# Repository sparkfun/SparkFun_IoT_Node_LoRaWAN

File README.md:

SparkFun IoT Node - LoRaWAN
========================================

[*SparkFun IoT Node - LoRaWAN (WRL-26060)*](https://www.sparkfun.com/products/26060)

The SparkFun IoT Node – LoRaWAN development board brings an entirely new level of usability to the often convoluted and configuration-intensive effort to set up a LoRaWAN™-based IoT Device. Combining the ease of LoRaWAN™ setup and configuration delivered by the Digi X-ON™ system with the rapid prototyping provided by the SparkFun Qwiic ecosystem, the SparkFun IoT Node – LoRaWAN development board accelerates IoT end-node creation and deployment.  

**Out of the Box**

With the integration of Digi X-ON™ technology, the SparkFun IoT Node – LoRaWAN board allows the creation and deployment of a LoRaWAN™ IoT sensor in minutes. 

* Set up the Digi HX15 Gateway for LoRaWAN and corresponding Digi account.  
* Register the IoT Node – LoRaWAN board quickly using the digital data block on the module.
* Add the antenna and a supported Qwiic sensor to the Node board 
* Power the board  

The SparkFun IoT Node – LoRaWAN board is shipped with firmware installed that Digi HX15 Gateway for LoRaWAN automatically connects to Digi X-ON, detects an attached sensor, and posts data to the X-ON cloud. Configured via a serial console connection, this application allows rapid evaluation and creation of a LoRaWAN™ IoT device.  

The pre-installed application is also open source and readily available, enabling rapid customization if desired.

**Firmware Development**

The firmware development for the SparkFun IoT Node – LoRaWAN board is performed primarily in the Arduino environment and enabled by an Arduino XBee® LR library from Digi. Combining the easy LoRaWAN™ access provided by the Digi library with the wide range of Qwiic sensors available from SparkFun, the possibilities of potential LoRaWAN™ IoT sensors are endless. 

Additionally, the pre-installed application is open source and readily available, enabling rapid customization if desired.  

**Hardware**

At the heart of the IoT Node – LoRaWAN board is the RP2350 microprocessor from Raspberry Pi, supporting many development environments, including Arduino, micropython, and the Raspberry Pi pico SDK. Besides the capabilities the RP2350 provides, we’ve kitted out the processer with all the goodies your project might require: 

* 16 MB of flash 
* 8 MB PSRAM 
* Qwiic connector 
* On-board Lithium Ion (LiPo) battery charging 
* Fuel gauge circuits 
* microSD card  
* A variety of IO pins 
* RGB LED and user button 

The Digi XBee® LR module for LoRaWAN module is directly connected to a serial port of the RP2350, allowing direct control and access to the LoRaWAN™ module via a development library provided by Digi.  

The XBee® LR for LoRaWAN™ module is the latest LoRaWAN™ module from Digi, delivering unmatched operational performance and onboarding simplicity. The Digi XBee® LR uses LoRa™ modulation for Non-Line-of-Sight (NLOS) two-way communications for long-range and high-noise RF environments. Since each module is pre-activated on Digi's X-ON™ cloud platform, automated connection and two-way device management are a breeze.

Repository Contents
-------------------

* **/Hardware** - KiCAD design files (.brd, .sch)
* **/Documents** - Files related to the hardware on the board
* **/docs** - Hookup guide files

Documentation
--------------
* **[Hookup Guide](https://docs.sparkfun.com/SparkFun_IoT_Node_LoRaWAN)** - Basic hookup guide for the SparkFun IoT Node for LoRaWAN®.
* **[Firmware Guide](https://docs.sparkfun.com/sfe-iot-node-lorawan/)** - Firmware guide for the SparkFun IoT Node for LoRaWAN®.

License Information
-------------------

This product is _**open source**_! 

Please review the LICENSE.md file for license information. 

If you have any questions or concerns on licensing, please contact technical support on our [SparkFun forums](https://forum.sparkfun.com/viewforum.php?f=152).

Distributed as-is; no warranty is given.

- Your friends at SparkFun.

_<COLLABORATION CREDIT>_

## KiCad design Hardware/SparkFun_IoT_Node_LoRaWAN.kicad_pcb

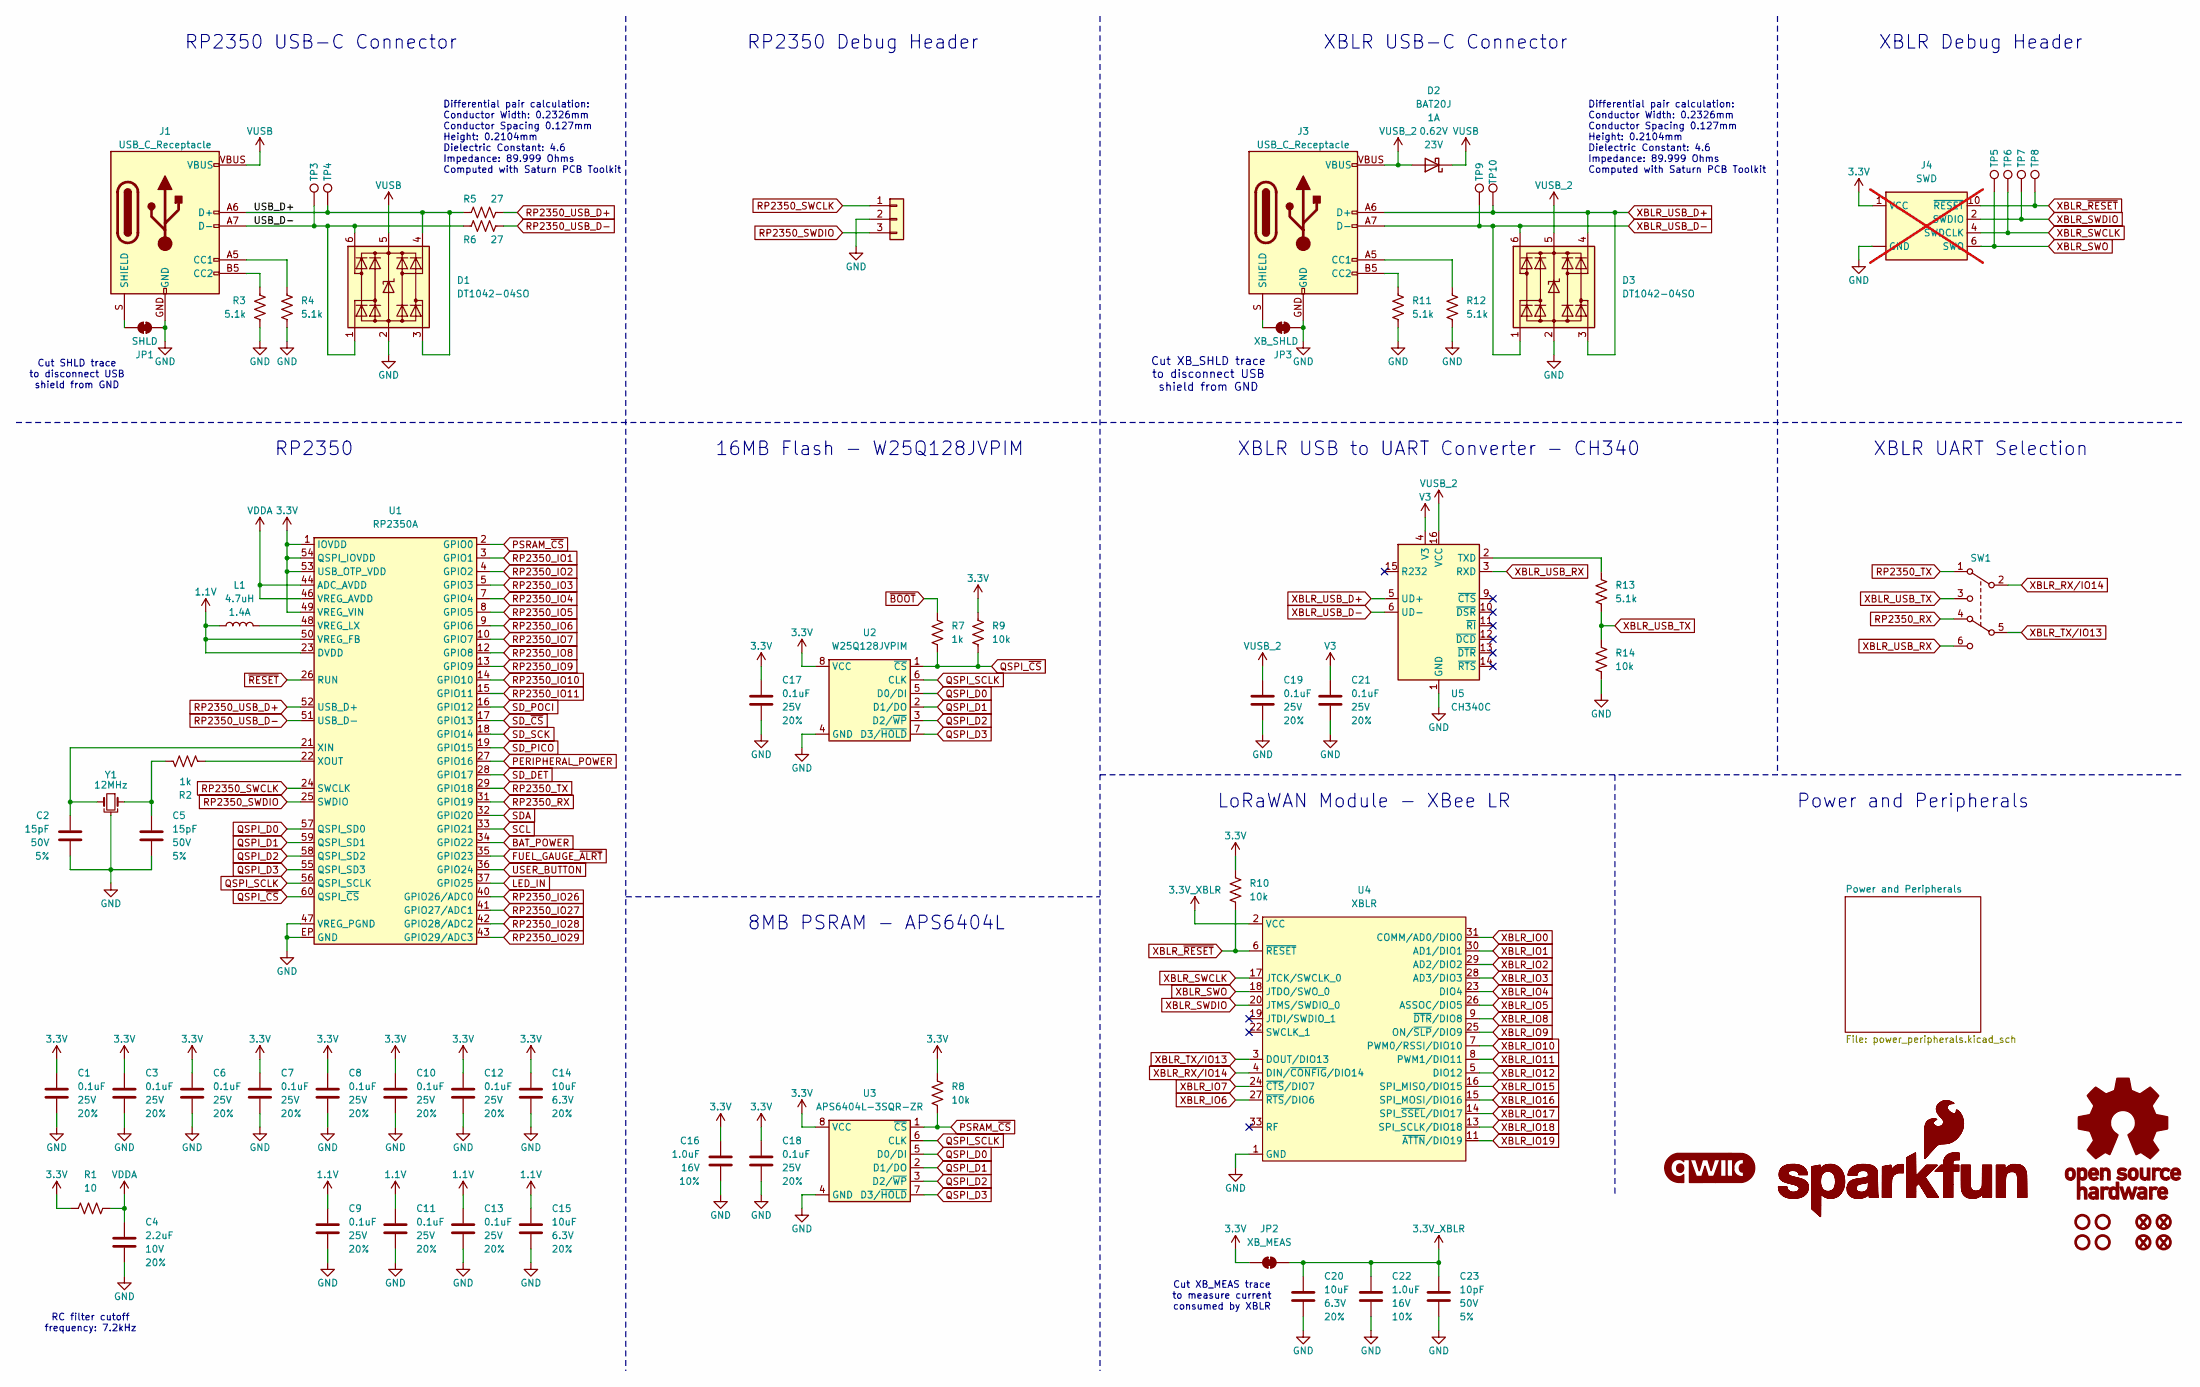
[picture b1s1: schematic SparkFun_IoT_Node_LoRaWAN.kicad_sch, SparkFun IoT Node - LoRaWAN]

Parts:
C1, C3, C6, C7, C8, C9, C10, C11, C12, C13, C17, C18, C19, C21: 0.1uF; C_0603_1608Metric; Voltage 25V; Tolerance 20%
C2, C5: 15pF; C_0603_1608Metric; Voltage 50V; Tolerance 5%
C4: 2.2uF; C_0603_1608Metric; Voltage 10V; Tolerance 20%
C14, C15, C20: 10uF; C_0603_1608Metric; Voltage 6.3V; Tolerance 20%
C16, C22: 1.0uF; C_0603_1608Metric; Voltage 16V; Tolerance 10%
C23: 10pF; C_0603_1608Metric; Voltage 50V; Tolerance 5%
D1, D3: DT1042-04SO; SOT23-6
D2: BAT20J; SOD-323
FID1, FID2, FID3, FID4: Fiducial_0.5mm; Fiducial_0.5mm_Mask1mm
G1: qwiic_Logo
G2: SparkFun_Logo; SparkFun_Logo_8mm
G3: SparkFun_Logo
G4: OSHW_Logo; Creative_Commons_License
J1, J3: USB_C_Receptacle; USB-C_16
J2: Conn_01x03; 1x03
J4: SWD; 2x5_1.27mm_SMD_Unshrouded; not fitted
JP1: SHLD; Jumper_2_NC_Trace
JP2: XB_MEAS; Jumper_2_PTH_SMD_Combo-NC
JP3: XB_SHLD; Jumper_2_NC_Trace
L1: 4.7uH; 1008_2520Metric
R1: 10; R_0603_1608Metric
R2, R7: 1k; R_0603_1608Metric
R3, R4, R11, R12, R13: 5.1k; R_0603_1608Metric
R5, R6: 27; R_0603_1608Metric
R8, R9, R10, R14: 10k; R_0603_1608Metric
ST1, ST2, ST3, ST4: Standoff
SW1: DPDT_Slide_SMD_7.2x3.5mm; Slide_DPDT_SMD_7.2x3.5mm; Mfg Part# ABC
TP3, TP4, TP5, TP6, TP7, TP8, TP9, TP10: 1.0mm; TestPoint-1.0mm
U1: RP2350A; QFN-60-1EP_7x7mm_P0.4mm_EP3.5x3.5mm
U2: W25Q128JVPIM; WDFN-8_6x5mm-SkinnyCenterPad
U3: APS6404L-3SQR-ZR; USON-8_3x2mm-SkinnyCenterPad
U4: XBLR; XBee_LR
U5: CH340C; SO-16
Y1: 12MHz; Crystal_SMD_2.5x2.0mm

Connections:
1.1V: C9.1, C11.1, C13.1, C15.1, L1.1, U1.6 (DVDD), U1.23 (DVDD), U1.39 (DVDD), U1.50 (VREG_FB)
3.3V: C1.1, C3.1, C6.1, C7.1, C8.1, C10.1, C12.1, C14.1, C16.1, C17.1, C18.1, J4.1 (VCC), JP2.1 (A), R1.2, R8.1, R9.1, R10.1, U1.1 (IOVDD), U1.11 (IOVDD), U1.20 (IOVDD), U1.30 (IOVDD), U1.38 (IOVDD), U1.45 (IOVDD), U1.49 (VREG_VIN), U1.53 (USB_OTP_VDD), U1.54 (QSPI_IOVDD), U2.8 (VCC), U3.8 (VCC); also elsewhere on the board
3.3V_XBLR: C20.1, C22.1, C23.1, JP2.2 (B), U4.2 (VCC)
/USB_D+: D1.3 (I/O2), D1.4 (I/O3), J1.A6 (D+), J1.B6 (D+), R5.2, TP4.1
/USB_D-: D1.1 (I/O1), D1.6 (I/O4), J1.A7 (D-), J1.B7 (D-), R6.2, TP3.1
BAT_POWER: U1.34 (GPIO22); also elsewhere on the board
FUEL_GAUGE_~ALRT: U1.35 (GPIO23); also elsewhere on the board
GND: C1.2, C2.1, C3.2, C4.2, C5.1, C6.2, C7.2, C8.2, C9.2, C10.2, C11.2, C12.2, C13.2, C14.2, C15.2, C16.2, C17.2, C18.2, C19.2, C20.2, C21.2, C22.2, C23.2, D1.2 (GND), D3.2 (GND), J1.GND, J2.2, J3.GND, J4.3 (GND), J4.5 (GND), J4.9 (GND), JP1.2 (B), JP3.2 (B), R3.2, R4.2, R11.2, R12.2, R14.2, U1.47 (VREG_PGND), U1.EP (GND), U2.4 (GND), U3.4 (GND), U3.9 (GND), U4.1 (GND), U4.10 (GND), U4.12 (GND), U4.21 (GND), U4.32 (GND), U4.34 (GND), U5.1 (GND), Y1.2, Y1.4; also elsewhere on the board
LED_IN: U1.37 (GPIO25); also elsewhere on the board
unnamed: C5.2, R2.2, Y1.1
unnamed: J1.A5 (CC1), R4.1
unnamed: J1.B5 (CC2), R3.1
unnamed: J1.S (SHIELD), JP1.1 (A)
unnamed: J3.A5 (CC1), R12.1
unnamed: J3.B5 (CC2), R11.1
unnamed: J3.S (SHIELD), JP3.1 (A)
unnamed: L1.2, U1.48 (VREG_LX)
unnamed: C2.2, U1.21 (XIN), Y1.3
unnamed: R2.1, U1.22 (XOUT)
unnamed: R13.1, U5.2 (TXD)
PERIPHERAL_POWER: U1.27 (GPIO16); also elsewhere on the board
PSRAM_~CS: R8.2, U1.2 (GPIO0), U3.1 (~CS)
QSPI_D0: U1.57 (QSPI_SD0), U2.5 (D0/DI), U3.5 (D0/DI)
QSPI_D1: U1.59 (QSPI_SD1), U2.2 (D1/DO), U3.2 (D1/DO)
QSPI_D2: U1.58 (QSPI_SD2), U2.3 (D2/~WP), U3.3 (D2/~WP)
QSPI_D3: U1.55 (QSPI_SD3), U2.7 (D3/~HOLD), U3.7 (D3/~HOLD)
QSPI_SCLK: U1.56 (QSPI_SCLK), U2.6 (CLK), U3.6 (CLK)
QSPI_~CS: R7.2, R9.2, U1.60 (QSPI_~CS), U2.1 (~CS)
RP2350_IO1: U1.3 (GPIO1); also elsewhere on the board
RP2350_IO2: U1.4 (GPIO2); also elsewhere on the board
RP2350_IO3: U1.5 (GPIO3); also elsewhere on the board
RP2350_IO4: U1.7 (GPIO4); also elsewhere on the board
RP2350_IO5: U1.8 (GPIO5); also elsewhere on the board
RP2350_IO6: U1.9 (GPIO6); also elsewhere on the board
RP2350_IO7: U1.10 (GPIO7); also elsewhere on the board
RP2350_IO8: U1.12 (GPIO8); also elsewhere on the board
RP2350_IO9: U1.13 (GPIO9); also elsewhere on the board
RP2350_IO10: U1.14 (GPIO10); also elsewhere on the board
RP2350_IO11: U1.15 (GPIO11); also elsewhere on the board
RP2350_IO26: U1.40 (GPIO26/ADC0); also elsewhere on the board
RP2350_IO27: U1.41 (GPIO27/ADC1); also elsewhere on the board
RP2350_IO28: U1.42 (GPIO28/ADC2); also elsewhere on the board
RP2350_IO29: U1.43 (GPIO29/ADC3); also elsewhere on the board
RP2350_RX: SW1.4 (A), U1.31 (GPIO19)
RP2350_SWCLK: J2.1, U1.24 (SWCLK)
RP2350_SWDIO: J2.3, U1.25 (SWDIO)
RP2350_TX: SW1.1 (A), U1.29 (GPIO18)
RP2350_USB_D+: R5.1, U1.52 (USB_D+)
RP2350_USB_D-: R6.1, U1.51 (USB_D-)
SCL: U1.33 (GPIO21); also elsewhere on the board
SDA: U1.32 (GPIO20); also elsewhere on the board
SD_DET: U1.28 (GPIO17); also elsewhere on the board
SD_PICO: U1.19 (GPIO15); also elsewhere on the board
SD_POCI: U1.16 (GPIO12); also elsewhere on the board
SD_SCK: U1.18 (GPIO14); also elsewhere on the board
SD_~CS: U1.17 (GPIO13); also elsewhere on the board
USER_BUTTON: U1.36 (GPIO24); also elsewhere on the board
V3: C21.1, U5.4 (V3)
VDDA: C4.1, R1.1, U1.44 (ADC_AVDD), U1.46 (VREG_AVDD); also elsewhere on the board
VUSB: D1.5 (VCC), D2.C, J1.VBUS; also elsewhere on the board
VUSB_2: C19.1, D2.A, D3.5 (VCC), J3.VBUS, U5.16 (VCC)
XBLR_IO0: U4.31 (COMM/AD0/DIO0); also elsewhere on the board
XBLR_IO1: U4.30 (AD1/DIO1); also elsewhere on the board
XBLR_IO2: U4.29 (AD2/DIO2); also elsewhere on the board
XBLR_IO3: U4.28 (AD3/DIO3); also elsewhere on the board
XBLR_IO4: U4.23 (DIO4); also elsewhere on the board
XBLR_IO5: U4.26 (ASSOC/DIO5); also elsewhere on the board
XBLR_IO6: U4.27 (~RTS/DIO6); also elsewhere on the board
XBLR_IO7: U4.24 (~CTS/DIO7); also elsewhere on the board
XBLR_IO8: U4.9 (~DTR/DIO8); also elsewhere on the board
XBLR_IO9: U4.25 (ON/~SLP/DIO9); also elsewhere on the board
XBLR_IO10: U4.7 (PWM0/RSSI/DIO10); also elsewhere on the board
XBLR_IO11: U4.8 (PWM1/DIO11); also elsewhere on the board
XBLR_IO12: U4.5 (DIO12); also elsewhere on the board
XBLR_IO15: U4.16 (SPI_MISO/DIO15); also elsewhere on the board
XBLR_IO16: U4.15 (SPI_MOSI/DIO16); also elsewhere on the board
XBLR_IO17: U4.14 (SPI_~SSEL/DIO17); also elsewhere on the board
XBLR_IO18: U4.13 (SPI_SCLK/DIO18); also elsewhere on the board
XBLR_IO19: U4.11 (~ATTN/DIO19); also elsewhere on the board
XBLR_RX/IO14: SW1.2 (B), U4.4 (DIN/~CONFIG/DIO14); also elsewhere on the board
XBLR_SWCLK: J4.4 (SWDCLK), TP6.1, U4.17 (JTCK/SWCLK_0)
XBLR_SWDIO: J4.2 (SWDIO), TP7.1, U4.20 (JTMS/SWDIO_0)
XBLR_SWO: J4.6 (SWO), TP5.1, U4.18 (JTDO/SWO_0)
XBLR_TX/IO13: SW1.5 (B), U4.3 (DOUT/DIO13); also elsewhere on the board
XBLR_USB_D+: D3.3 (I/O2), D3.4 (I/O3), J3.A6 (D+), J3.B6 (D+), TP10.1, U5.5 (UD+)
XBLR_USB_D-: D3.1 (I/O1), D3.6 (I/O4), J3.A7 (D-), J3.B7 (D-), TP9.1, U5.6 (UD-)
XBLR_USB_RX: SW1.6 (C), U5.3 (RXD)
XBLR_USB_TX: R13.2, R14.1, SW1.3 (C)
XBLR_~RESET: J4.10 (~RESET), R10.2, TP8.1, U4.6 (~RESET)
~BOOT: R7.1; also elsewhere on the board
~RESET: U1.26 (RUN); also elsewhere on the board

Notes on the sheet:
Differential pair calculation: Conductor Width: 0.2326mm Conductor Spacing 0.127mm Height: 0.2104mm Dielectric Constant: 4.6 Impedance: 89.999 Ohms Computed with Saturn PCB Toolkit
16MB Flash - W25Q128JVPIM
8MB PSRAM - APS6404L
XBLR USB-C Connector
RP2350 Debug Header
XBLR USB to UART Converter - CH340
RP2350
Cut XB_MEAS trace to measure current consumed by XBLR
Cut SHLD trace to disconnect USB shield from GND
XBLR Debug Header
RC filter cutoff frequency: 7.2kHz
Cut XB_SHLD trace to disconnect USB shield from GND
LoRaWAN Module - XBee LR
XBLR UART Selection
RP2350 USB-C Connector
Power and Peripherals

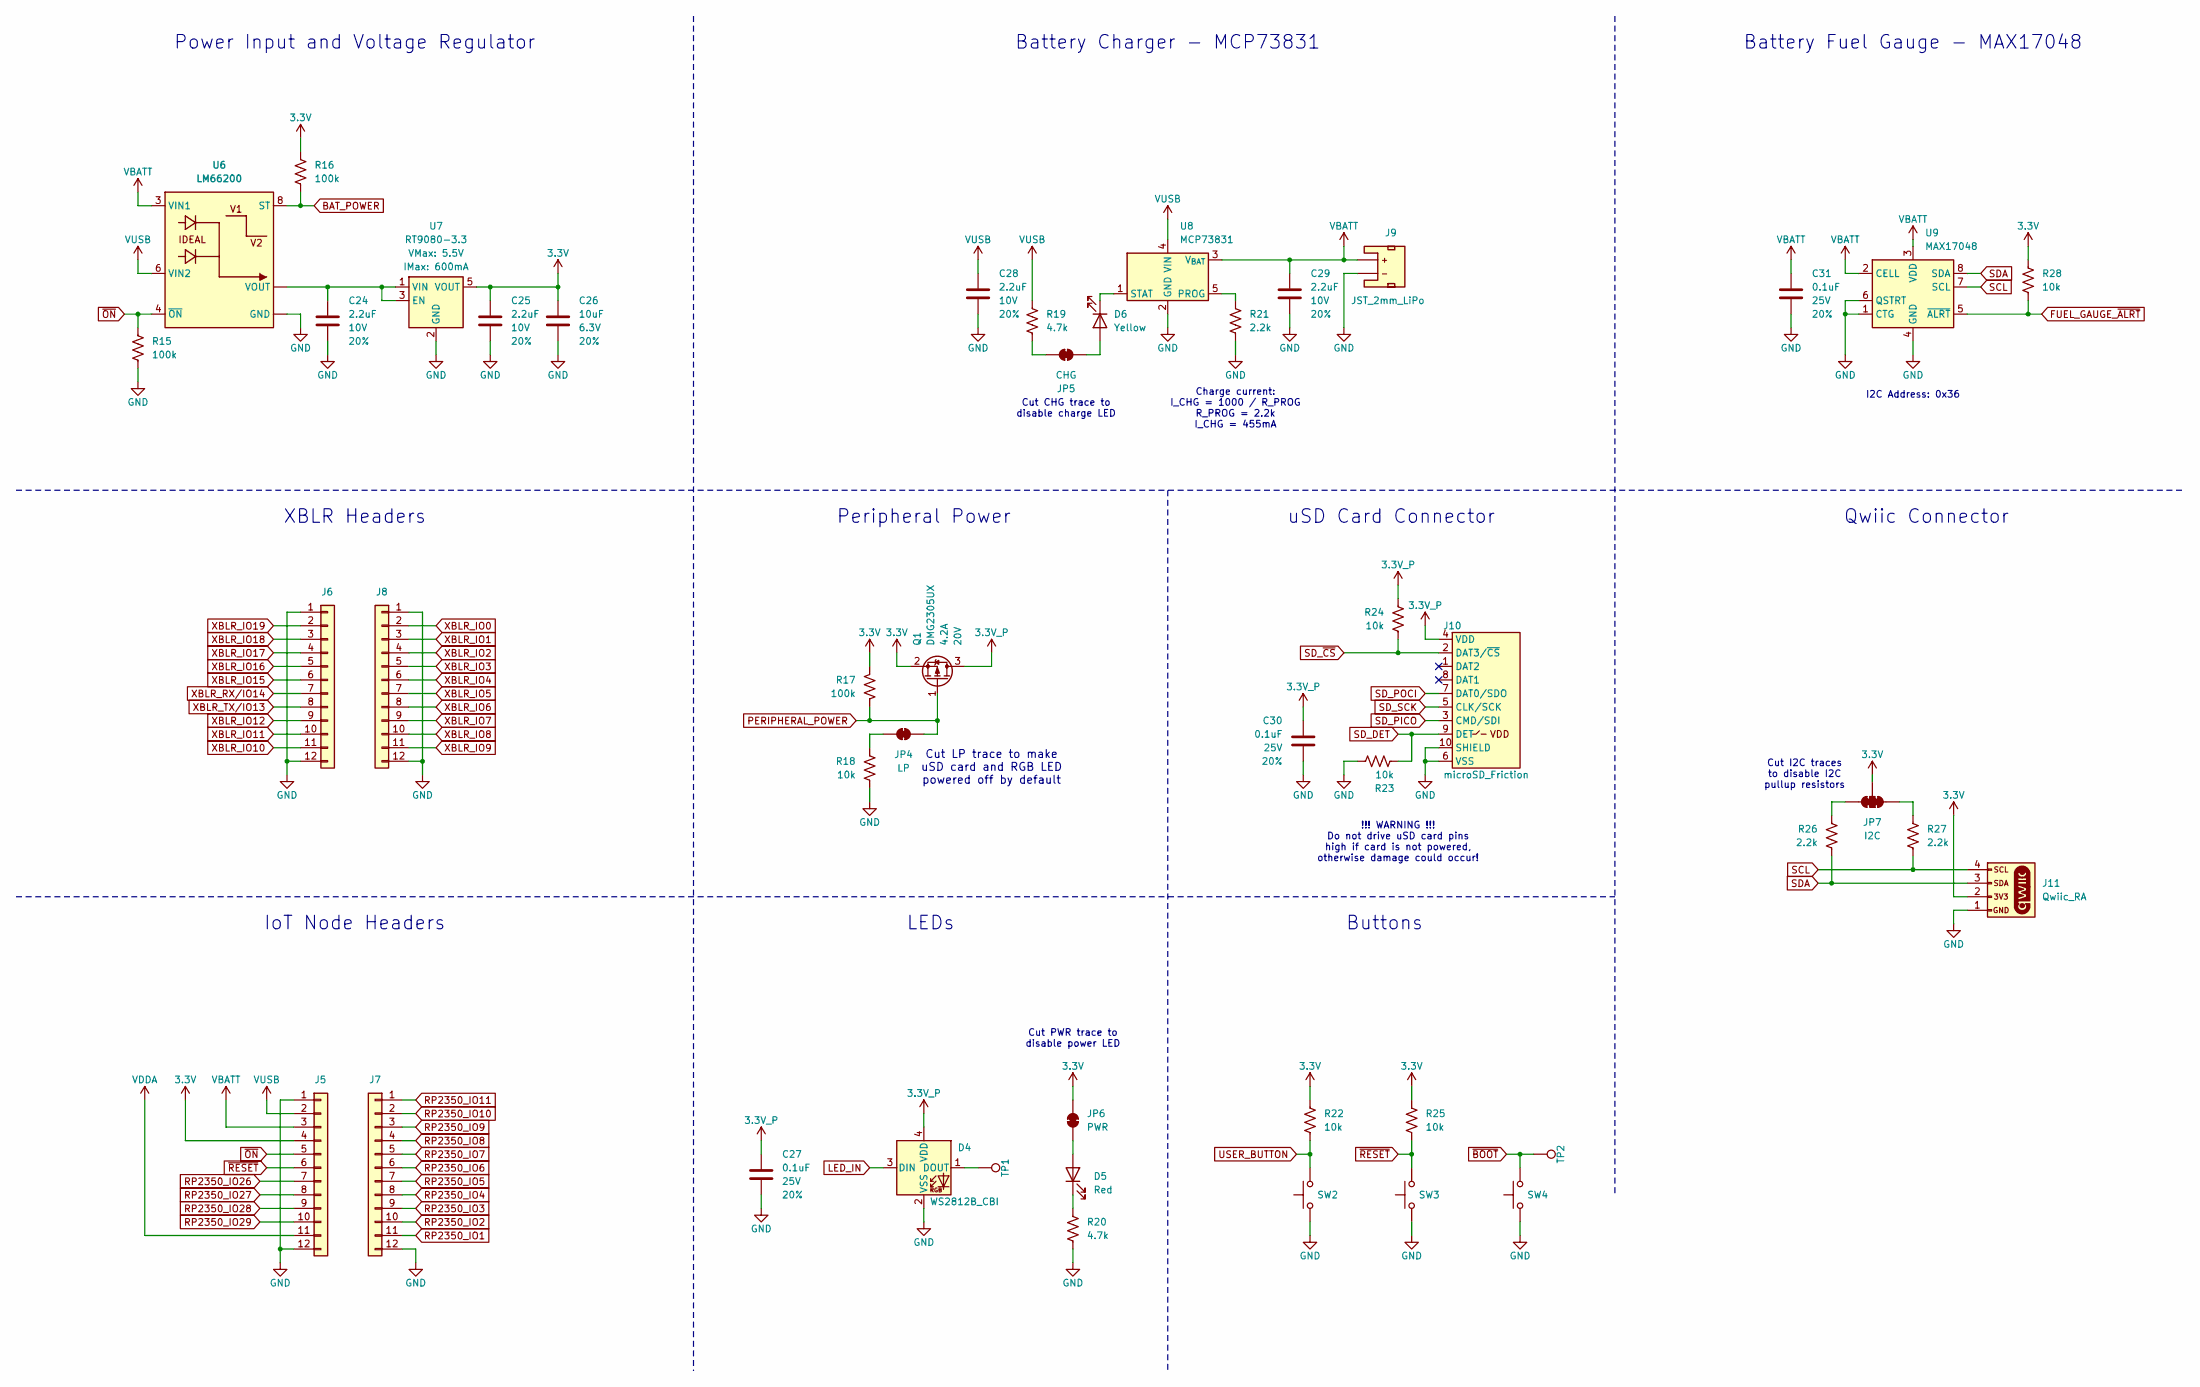
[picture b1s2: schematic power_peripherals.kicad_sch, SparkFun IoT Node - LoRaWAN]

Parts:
C24, C25, C28, C29: 2.2uF; C_0603_1608Metric; Voltage 10V; Tolerance 20%
C26: 10uF; C_0603_1608Metric; Voltage 6.3V; Tolerance 20%
C27, C30, C31: 0.1uF; C_0603_1608Metric; Voltage 25V; Tolerance 20%
D4: WS2812B_CBI; WS2812_2020
D5: Red; LED_0603_1608Metric_Red
D6: Yellow; LED_0603_1608Metric_Yellow
J5, J6, J7, J8: Conn_01x10; 1x12
J9: JST_2mm_LiPo; JST_SMD_2.0mm-2
J10: microSD_Friction; microSD_Friction_Fit_Common
J11: Qwiic_RA; JST_SMD_1.0mm-4_RA
JP4: LP; Jumper_2_NC_Trace
JP5: CHG; Jumper_2_NC_Trace
JP6: PWR; Jumper_2_NC_Trace
JP7: I2C; Jumper_3_NC-2_Trace
Q1: DMG2305UX; SOT23-3
R15, R16, R17: 100k; R_0603_1608Metric
R18, R22, R23, R24, R25, R28: 10k; R_0603_1608Metric
R19, R20: 4.7k; R_0603_1608Metric
R21, R26, R27: 2.2k; R_0603_1608Metric
SW2, SW3, SW4: SMD_4.6x2.8mm_h2.5mm; Push_SMD_4.6x2.8mm_h2.5mm
TP1, TP2: 1.0mm; TestPoint-1.0mm
U6: LM66200; SOT-583-8
U7: RT9080-3.3; SOT23-5
U8: MCP73831; SOT23-5
U9: MAX17048; DFN-8

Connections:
3.3V: C25.1, C26.1, J5.4, J11.2, JP6.2 (B), JP7.2 (C), Q1.2 (S), R16.1, R17.1, R22.1, R25.1, R28.1, U7.5 (VOUT); also elsewhere on the board
3.3V_P: C27.1, C30.1, D4.4 (VDD), J10.4 (VDD), Q1.3 (D), R24.1
BAT_POWER: R16.2, U6.8 (ST); also elsewhere on the board
FUEL_GAUGE_~ALRT: R28.2, U9.5 (~ALRT); also elsewhere on the board
GND: C24.2, C25.2, C26.2, C27.2, C28.2, C29.2, C30.2, C31.2, D4.2 (VSS), J5.1, J5.12, J6.1, J6.12, J7.12, J8.1, J8.12, J9.1 (-), J10.6 (VSS), J10.10 (SHIELD), J11.1, R15.2, R18.2, R20.2, R21.2, R23.2, SW2.1, SW3.1, SW4.1, U6.1 (GND), U6.5 (GND), U7.2 (GND), U8.2 (GND), U9.1 (CTG), U9.4 (GND), U9.6 (QSTRT), U9.9 (GND); also elsewhere on the board
LED_IN: D4.3 (DIN); also elsewhere on the board
unnamed: D4.1 (DOUT), TP1.1
unnamed: D5.2 (A), JP6.1 (A)
unnamed: D5.1 (K), R20.1
unnamed: D6.2 (A), JP5.2 (B)
unnamed: D6.1 (K), U8.1 (STAT)
unnamed: JP4.1 (A), R18.1
unnamed: JP5.1 (A), R19.2
unnamed: JP7.1 (A), R27.1
unnamed: JP7.3 (B), R26.1
unnamed: C24.1, U6.2 (VOUT), U6.7 (VOUT), U7.1 (VIN), U7.3 (EN)
unnamed: R21.1, U8.5 (PROG)
PERIPHERAL_POWER: JP4.2 (B), Q1.1 (G), R17.2; also elsewhere on the board
RP2350_IO1: J7.11; also elsewhere on the board
RP2350_IO2: J7.10; also elsewhere on the board
RP2350_IO3: J7.9; also elsewhere on the board
RP2350_IO4: J7.8; also elsewhere on the board
RP2350_IO5: J7.7; also elsewhere on the board
RP2350_IO6: J7.6; also elsewhere on the board
RP2350_IO7: J7.5; also elsewhere on the board
RP2350_IO8: J7.4; also elsewhere on the board
RP2350_IO9: J7.3; also elsewhere on the board
RP2350_IO10: J7.2; also elsewhere on the board
RP2350_IO11: J7.1; also elsewhere on the board
RP2350_IO26: J5.7; also elsewhere on the board
RP2350_IO27: J5.8; also elsewhere on the board
RP2350_IO28: J5.9; also elsewhere on the board
RP2350_IO29: J5.10; also elsewhere on the board
SCL: J11.4, R27.2, U9.7 (SCL); also elsewhere on the board
SDA: J11.3, R26.2, U9.8 (SDA); also elsewhere on the board
SD_DET: J10.9 (DET), R23.1; also elsewhere on the board
SD_PICO: J10.3 (CMD/SDI); also elsewhere on the board
SD_POCI: J10.7 (DAT0/SDO); also elsewhere on the board
SD_SCK: J10.5 (CLK/SCK); also elsewhere on the board
SD_~CS: J10.2 (DAT3/~CS), R24.2; also elsewhere on the board
USER_BUTTON: R22.2, SW2.2; also elsewhere on the board
VBATT: C29.1, C31.1, J5.3, J9.2 (+), U6.3 (VIN1), U8.3 (V_{BAT}), U9.2 (CELL), U9.3 (VDD)
VDDA: J5.11; also elsewhere on the board
VUSB: C28.1, J5.2, R19.1, U6.6 (VIN2), U8.4 (VIN); also elsewhere on the board
XBLR_IO0: J8.2; also elsewhere on the board
XBLR_IO1: J8.3; also elsewhere on the board
XBLR_IO2: J8.4; also elsewhere on the board
XBLR_IO3: J8.5; also elsewhere on the board
XBLR_IO4: J8.6; also elsewhere on the board
XBLR_IO5: J8.7; also elsewhere on the board
XBLR_IO6: J8.8; also elsewhere on the board
XBLR_IO7: J8.9; also elsewhere on the board
XBLR_IO8: J8.10; also elsewhere on the board
XBLR_IO9: J8.11; also elsewhere on the board
XBLR_IO10: J6.11; also elsewhere on the board
XBLR_IO11: J6.10; also elsewhere on the board
XBLR_IO12: J6.9; also elsewhere on the board
XBLR_IO15: J6.6; also elsewhere on the board
XBLR_IO16: J6.5; also elsewhere on the board
XBLR_IO17: J6.4; also elsewhere on the board
XBLR_IO18: J6.3; also elsewhere on the board
XBLR_IO19: J6.2; also elsewhere on the board
XBLR_RX/IO14: J6.7; also elsewhere on the board
XBLR_TX/IO13: J6.8; also elsewhere on the board
~BOOT: SW4.2, TP2.1; also elsewhere on the board
~ON: J5.5, R15.1, U6.4 (~ON)
~RESET: J5.6, R25.2, SW3.2; also elsewhere on the board

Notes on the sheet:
LEDs
Buttons
Cut LP trace to make uSD card and RGB LED powered off by default
I2C Address: 0x36
Charge current: I_CHG = 1000 / R_PROG R_PROG = 2.2k I_CHG = 455mA
Cut CHG trace to disable charge LED
Peripheral Power
Battery Charger - MCP73831
!!! WARNING !!! Do not drive uSD card pins high if card is not powered, otherwise damage could occur!
Cut I2C traces to disable I2C pullup resistors
uSD Card Connector
IoT Node Headers
Power Input and Voltage Regulator
XBLR Headers
Cut PWR trace to disable power LED
Battery Fuel Gauge - MAX17048
Qwiic Connector

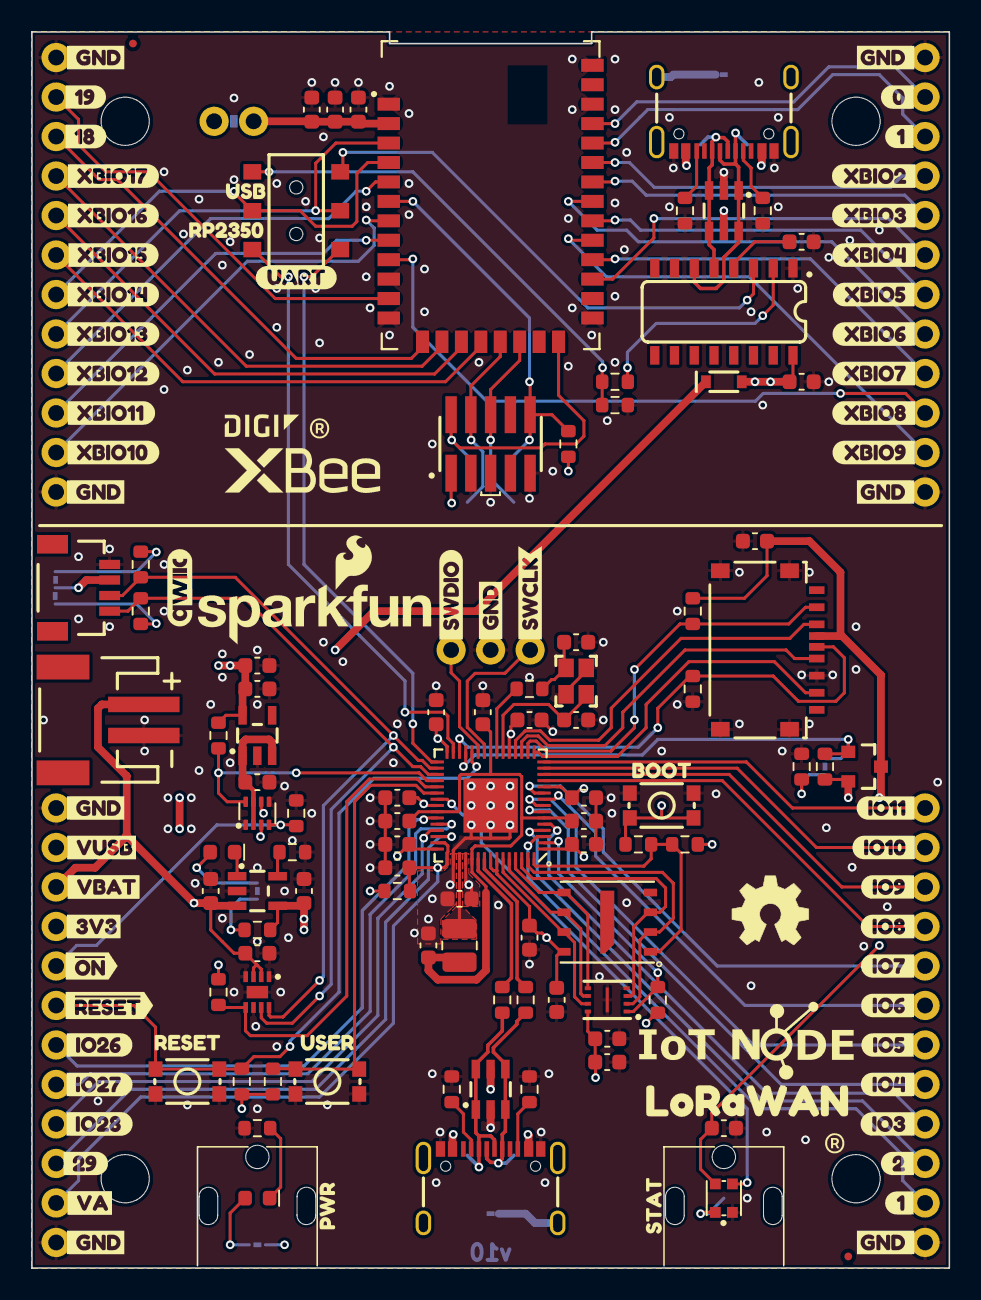
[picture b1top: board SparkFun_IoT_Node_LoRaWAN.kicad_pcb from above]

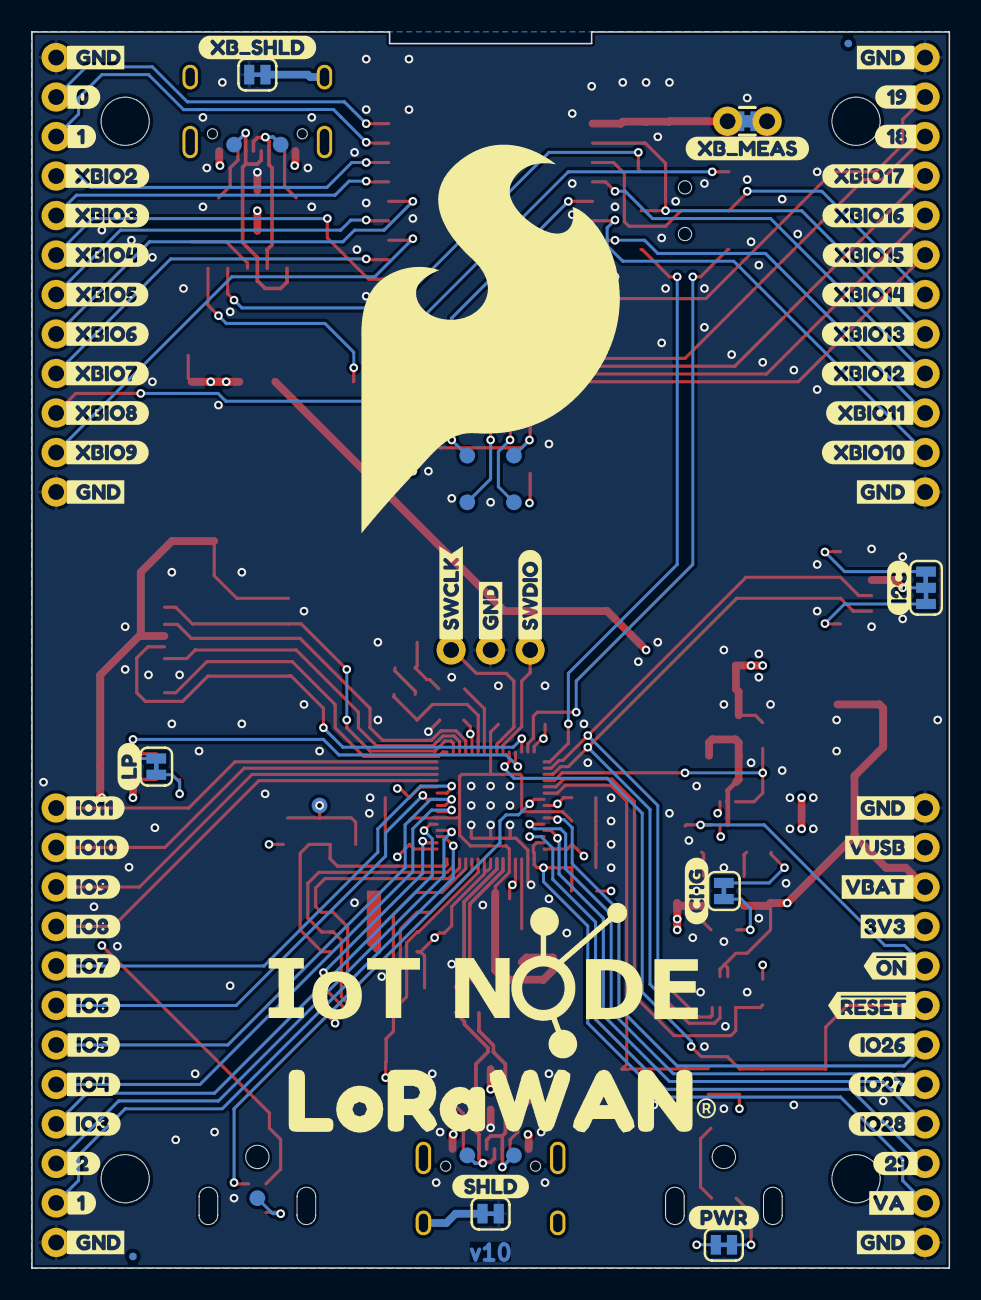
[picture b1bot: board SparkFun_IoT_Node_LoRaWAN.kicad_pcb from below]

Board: 4 copper layers, 59.0 x 79.5 mm, 238 parts (78 on the bottom side), 105 nets.

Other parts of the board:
Ref**: Val**; OSHW_Logo_5mm
kibuzzard-669A9B0A: G***; kibuzzard-669A9B0A
kibuzzard-669E9F4F: G***; kibuzzard-669E9F4F
kibuzzard-669E9F62: G***; kibuzzard-669E9F62
kibuzzard-669E97BF: G***; kibuzzard-669E97BF
kibuzzard-669E97C2: G***; kibuzzard-669E97C2
kibuzzard-669E97C7: G***; kibuzzard-669E97C7
kibuzzard-669E97CC: G***; kibuzzard-669E97CC
kibuzzard-669E97CF: G***; kibuzzard-669E97CF
kibuzzard-669E97D3: G***; kibuzzard-669E97D3
kibuzzard-669E97D7: G***; kibuzzard-669E97D7
kibuzzard-669E97DA: G***; kibuzzard-669E97DA
kibuzzard-669E976B: G***; kibuzzard-669E976B
kibuzzard-669E977C: G***; kibuzzard-669E977C
kibuzzard-669E977F: G***; kibuzzard-669E977F
kibuzzard-669E978A: G***; kibuzzard-669E978A
kibuzzard-669E978E: G***; kibuzzard-669E978E
kibuzzard-669E979E: G***; kibuzzard-669E979E
kibuzzard-669E9751: G***; kibuzzard-669E9751
kibuzzard-669E9757: G***; kibuzzard-669E9757
kibuzzard-669E9763: G***; kibuzzard-669E9763
kibuzzard-669E9784: G***; kibuzzard-669E9784
kibuzzard-669E9793: G***; kibuzzard-669E9793
kibuzzard-669E9798: G***; kibuzzard-669E9798
kibuzzard-669EA03D: G***; kibuzzard-669EA03D
kibuzzard-669EA04A: G***; kibuzzard-669EA04A
kibuzzard-669EA05B: G***; kibuzzard-669EA05B
kibuzzard-669EA5B0: G***; kibuzzard-669EA5B0
kibuzzard-669EA5C9: G***; kibuzzard-669EA5C9
kibuzzard-669EA5FC: G***; kibuzzard-669EA5FC
kibuzzard-669EA026: G***; kibuzzard-669EA026
kibuzzard-669EA63A: G***; kibuzzard-669EA63A
kibuzzard-669EA63F: G***; kibuzzard-669EA63F
kibuzzard-669EA64A: G***; kibuzzard-669EA64A
kibuzzard-669EA64E: G***; kibuzzard-669EA64E
kibuzzard-669EA604: G***; kibuzzard-669EA604
kibuzzard-669EA643: G***; kibuzzard-669EA643
kibuzzard-669EA654: G***; kibuzzard-669EA654
kibuzzard-669EC8FA: G***; kibuzzard-669EC8FA
kibuzzard-669ED447: G***; kibuzzard-669ED447
kibuzzard-671A9B5A: G***; kibuzzard-671A9B5A
kibuzzard-671A9B9C: G***; kibuzzard-671A9B9C
kibuzzard-671A9B60: G***; kibuzzard-671A9B60
kibuzzard-671A9B96: G***; kibuzzard-671A9B96
kibuzzard-671A9BD9: G***; kibuzzard-671A9BD9
kibuzzard-671A9BE0: G***; kibuzzard-671A9BE0
kibuzzard-671A9C1E: G***; kibuzzard-671A9C1E
kibuzzard-671A9C23: G***; kibuzzard-671A9C23
kibuzzard-671A9C32: G***; kibuzzard-671A9C32
kibuzzard-671A9C38: G***; kibuzzard-671A9C38
kibuzzard-671A9CA4: G***; kibuzzard-671A9CA4
kibuzzard-671A9CA8: G***; kibuzzard-671A9CA8
kibuzzard-6691B3A2, kibuzzard-6691B3A2#2, kibuzzard-6691B3A2#3, kibuzzard-6691B3A2#4, kibuzzard-6691B3A2#5, kibuzzard-6691B3A2#6, kibuzzard-6691B3A2#7: G***; kibuzzard-6691B3A2
kibuzzard-6691B3CB: G***; kibuzzard-6691B3CB
kibuzzard-6691B3E7: G***; kibuzzard-6691B3E7
kibuzzard-6691B3EC: G***; kibuzzard-6691B3EC
kibuzzard-6691B3F1: G***; kibuzzard-6691B3F1
kibuzzard-6691B3F5: G***; kibuzzard-6691B3F5
kibuzzard-6691B3F9: G***; kibuzzard-6691B3F9
kibuzzard-6691B3FD: G***; kibuzzard-6691B3FD
kibuzzard-6691B4CC: G***; kibuzzard-6691B4CC
kibuzzard-6691B5FB: G***; kibuzzard-6691B5FB
kibuzzard-6691B6A1: G***; kibuzzard-6691B6A1
kibuzzard-6691B6A6: G***; kibuzzard-6691B6A6
kibuzzard-6691B6AB: G***; kibuzzard-6691B6AB
kibuzzard-6691B6B0: G***; kibuzzard-6691B6B0
kibuzzard-6691B6B5: G***; kibuzzard-6691B6B5
kibuzzard-6691B6B9: G***; kibuzzard-6691B6B9
kibuzzard-6691B6EC: G***; kibuzzard-6691B6EC
kibuzzard-6691B7AB, kibuzzard-6691B7AB#2: G***; kibuzzard-6691B7AB
kibuzzard-6691B7BF, kibuzzard-6691B7BF#2: G***; kibuzzard-6691B7BF
kibuzzard-6691B8D3: G***; kibuzzard-6691B8D3
kibuzzard-6691B8DD: G***; kibuzzard-6691B8DD
kibuzzard-6691B43C: G***; kibuzzard-6691B43C
kibuzzard-6691B44C: G***; kibuzzard-6691B44C
kibuzzard-6691B48E: G***; kibuzzard-6691B48E
kibuzzard-6691B60A: G***; kibuzzard-6691B60A
kibuzzard-6691B62B: G***; kibuzzard-6691B62B
kibuzzard-6691B62F: G***; kibuzzard-6691B62F
kibuzzard-6691B72F: G***; kibuzzard-6691B72F
kibuzzard-6691B73B: G***; kibuzzard-6691B73B
kibuzzard-6691B276, kibuzzard-6691B276#2, kibuzzard-6691B276#3, kibuzzard-6691B276#4, kibuzzard-6691B276#5, kibuzzard-6691B276#6, kibuzzard-6691B276#7, kibuzzard-6691B276#8, kibuzzard-6691B276#9: G***; kibuzzard-6691B276
kibuzzard-6691B296: G***; kibuzzard-6691B296
kibuzzard-6691B419: G***; kibuzzard-6691B419
kibuzzard-6691B440: G***; kibuzzard-6691B440
kibuzzard-6691B444: G***; kibuzzard-6691B444
kibuzzard-6691B448: G***; kibuzzard-6691B448
kibuzzard-6691B450: G***; kibuzzard-6691B450
kibuzzard-6691B472: G***; kibuzzard-6691B472
kibuzzard-6691B623: G***; kibuzzard-6691B623
kibuzzard-6691B627: G***; kibuzzard-6691B627
kibuzzard-6691B633: G***; kibuzzard-6691B633
kibuzzard-6691B637: G***; kibuzzard-6691B637
kibuzzard-6691B649: G***; kibuzzard-6691B649
kibuzzard-6691B661: G***; kibuzzard-6691B661
kibuzzard-6691B670: G***; kibuzzard-6691B670
kibuzzard-6691B712: G***; kibuzzard-6691B712
kibuzzard-6691B750: G***; kibuzzard-6691B750
kibuzzard-6691B763: G***; kibuzzard-6691B763
kibuzzard-6691B872: G***; kibuzzard-6691B872
kibuzzard-6691B926: G***; kibuzzard-6691B926
kibuzzard-6691B931: G***; kibuzzard-6691B931
kibuzzard-6691B952: G***; kibuzzard-6691B952
kibuzzard-66999523: G***; kibuzzard-66999523

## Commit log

2024-07-02 Add initial design
    Create symbol and footprint for XBLR
    Majority of schematic components, still missing headers and need to determine pinouts
    Initial board dimensions set, components placed but not arranged, and nothing routed
2024-07-03 v01 schematic updates
    Add remaining schematic components
    Split schematic into multiple sheets
    Still need to define pinouts for RP2350, XBLR, and headers
2024-07-08 Initial board layout
    Board outline determined based off selected enclosure
    Clusters of components placed and routed
    Waiting for feedback before finishing routing
2024-07-11 Review updates
    Remove region selection resistors
    Add uSD card connector
    Move XBLR USB connector within enclosure
2024-07-12 Finish connections and routing
2024-07-12 Add silk labels to UART switch
2024-07-12 Add level shifter to CH340 TX pin
2024-07-15 Improve GND stitching
    Add lots of GND vias
    Nudge tracks to connect GND pour regions
2024-07-15 Clean up schematic
    Add lines between regions
    Add instruction text to all jumpers
2024-07-18 Update project libraries
    Add RP2350
    Update XBLR to KiCad standards
2024-07-18 v02 Schematic Updates
    Bump version number to v02
    Fix RP2350, APS6404L, and 12MHz crystal to use proper KiCad symbols and footprints instead of imported from Eagle
    Change schematic to use 2x Ledger sheets
    Change Qwiic connector to power from 3.3V
    Change user button and RGB LED to small mount versions
    Split headers into XBLR and IoT Node specific regions
2024-07-18 v02 Board Updates
    Still in progress...
    Bump version number to v02
    Update RP2350, APS6404L, and 12MHz crystal footprints
    Move USB-C connector to be centered, and not go through wall of enclosure
    Move power LED and RGB LED to be symmetric along south edge of board
    Move battery connector, Qwiic connector, and uSD card connector to middle edges of board
2024-07-22 Finish v02 updates
    Clean up schematic
    Add test points for boot button and RGB LED output
    Update pinouts of headers and RP2350
    Fix pad shape of XBLR footprint
    Finish routing
    Update logos
2024-07-22 Add chungus SparkFun flame to back silkcreen
2024-07-24 Re-annotate schematic
2024-07-24 Design review updates
    Fix typo in USB calculations
    Space out buttons in schematic
    Add courtyard to flash memory
    Reposition measures outside of enclosure outline
    Reposition LEd silk outside of light pipe footprint
2024-07-24 Design review updates
    Move text for D1 and D3 to not overlap wire
    Add regulator max output current
    Add battery charge current
    Add (R) to LoRaWAN silkscreen
    Name copper zones
    Nudge mesaure text on let side to not overlap lines
2024-07-24 Update board stackup
2024-07-24 Make jumper reference designators visible
2024-07-24 Cosmetic tweaks
    Nudge IO 29 silk away from mounting hole
    Add VDDA RC filter cutoff frequency
2024-07-24 Move STAT silk
2024-07-24 Spread out reset and user buttons
2024-07-24 Add soldermask cutout for CBI footprints
2024-07-24 Add v02 production files
2024-10-23 Update dimensions of box
    Accidentally used the top dimensions instead of bottom dimensions. Board needs to shrink.
2024-10-24 Shrink board to fit new enclosure dimensions
2024-10-24 Symbol and footprint update
2024-10-24 Bump version number to v10
2024-10-24 Fix IoT Node Logo
    Lines were poking into the O of Node for some reason. "Stroke to path" in InkScape fixed it.
    Also add SVG of logo
2024-10-24 Fix dimension of debug header
2024-10-24 Fix dimensions of board
2024-10-29 Design review updates
    Fix layers to standard SFE usage
    Add link to enclosure and PDF of dimensions
    Move fiducials away from PTH pads
    Add USB test points
    Add XBLR debug test points
2024-10-30 Add XBLR 3D model
    Also fix RP2350A library reference
2024-10-30 Set XBLR debug header to DNP
2024-10-30 Add OSHW logo to silkscreen
2024-11-04 Add v10 production files
2024-11-04 Checklist update
    Update 1.4A inductor
    Update date design
    Add I2C address of fuel gauge
2024-11-18 Library update
2024-12-02 Set SWD header as DNP in board file
2025-01-02 Initial check in of documentation
2025-01-02 Updating product name and trademark info
2025-01-04 Updates to GDS and Resources
2025-01-04 Updating GDS
2025-01-05 Updating GDS and Product Name
2025-01-05 Removing extra lines
2025-01-06 Fix print orientation
2025-01-09 Deployed b066987 with MkDocs version: 1.6.1
2025-05-02 Update quick_start.md
    Adding recommendation for using phone camera for scanning data matrix on XBee.
2025-05-02 Updating build file
    Adding updated build file for GH Pages.
2025-05-02 Deployed 14026ee with MkDocs version: 1.6.1
2025-05-02 Update quick_start.md
    Removing button formatting to fix rendering.
2025-05-02 Deployed 6870991 with MkDocs version: 1.6.1
2025-05-02 Update quick_start.md
    Attempt #2 to fix button rendering.
2025-05-02 Deployed 4455050 with MkDocs version: 1.6.1
2025-05-02 Update quick_start.md
    Removing login button since it's not rendering properly.
2025-05-02 Deployed 8b37aee with MkDocs version: 1.6.1
2026-06-03 Deployed 6a37f1d with MkDocs version: 1.6.1

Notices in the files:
parts and their libraries:
Released under the Creative Commons Attribution Share-Alike 4.0 License
https://creativecommons.org/licenses/by-sa/4.0
